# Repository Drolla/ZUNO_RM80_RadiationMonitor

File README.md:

# Z-Wave enabled Radiation, Temperature and Humidity Monitor with LCD Display

## Table of Contents

* [Description](#description)
* [Hardware required](#hardware-required)
* [Schematics, PCB layout](#schematics-pcb-layout)
* [Photos](#photos)
* [Release history](#release-history)
* [License](#license)

## Description

The project requires the following hardware components:
  * Z-Uno (Z-Wave) development board from Z-Wave.Me
  * Radiation monitor - RM-60/70/80 radiation monitor from AWARE Electronics. Connected to the external interrupt ZUNO_EXT_ZEROX.
  * Temperature/humidity sensor - DHT22 temp/hum sensor, 10kOhm resistor. Controlled via a single pin using the ZUNO_DHT module.
  * LCD display - Adafruit Sharp 1.3" Memory LCD Display. Controlled via the SPI interface.
  * Control buttons - 2 simple press buttons connected to 2 DIOs.

In addition to the functions related to the above hardware components, the application provides the following features:
  * Radiation data, temperature and humidity can be reported every minutes via Z-Wave
  * Radiation events can be indicated via the Z-Uno user LED
  * Status information can be reported via the USB attached serial interface
  * Configuration options: Z-Wave reporting, LED activity and status reporting via serial interface can individually be enabled or disabled. Configurations are stored in the EEPROM and restored after power cycling.

## Hardware required

  * Z-Uno board
  * RM-60/70/80 radiation monitor from AWARE Electronics
  * Sensor DHT11
  * LCD display - Adafruit Sharp 1.3" Memory LCD Display
  * 1 resistor1 10kOhm
  * 2 press buttons
  * Breadboard, wires

-  -  -  -  -  -  -  -  -  -  -  -  -  -  -  -  -  -  -  -  -

## Schematics, PCB layout

Schematic:

PCB layout:

Breadboard:

-  -  -  -  -  -  -  -  -  -  -  -  -  -  -  -  -  -  -  -  -

## Photos

Breadboard:

Final device:

Some display pictures:

-  -  -  -  -  -  -  -  -  -  -  -  -  -  -  -  -  -  -  -  -

## Release history

* 0.1
    * Initial version, verified with Z-Uno firmware revision 2.0.7. Since no external interrupts are supported in this firmware revision, the RM-80 radiation monitor has to be connected to the serial interface Serial0.
* 0.2
    * Version adapted for Z-Uno firmware version 2.0.9 that supports external interrupts. The RM-80 radiation monitor has to be connected to the external interrupt 'ZUNO_EXT_ZEROX'.
	 * Only valid mean/average values are reported via Z-Wave (e.g. 1-hour average value will not be reported the 1st hour after booting)

-  -  -  -  -  -  -  -  -  -  -  -  -  -  -  -  -  -  -  -  -

## License

This project is licensed under the MIT License - see the _LICENSE_ file for details.

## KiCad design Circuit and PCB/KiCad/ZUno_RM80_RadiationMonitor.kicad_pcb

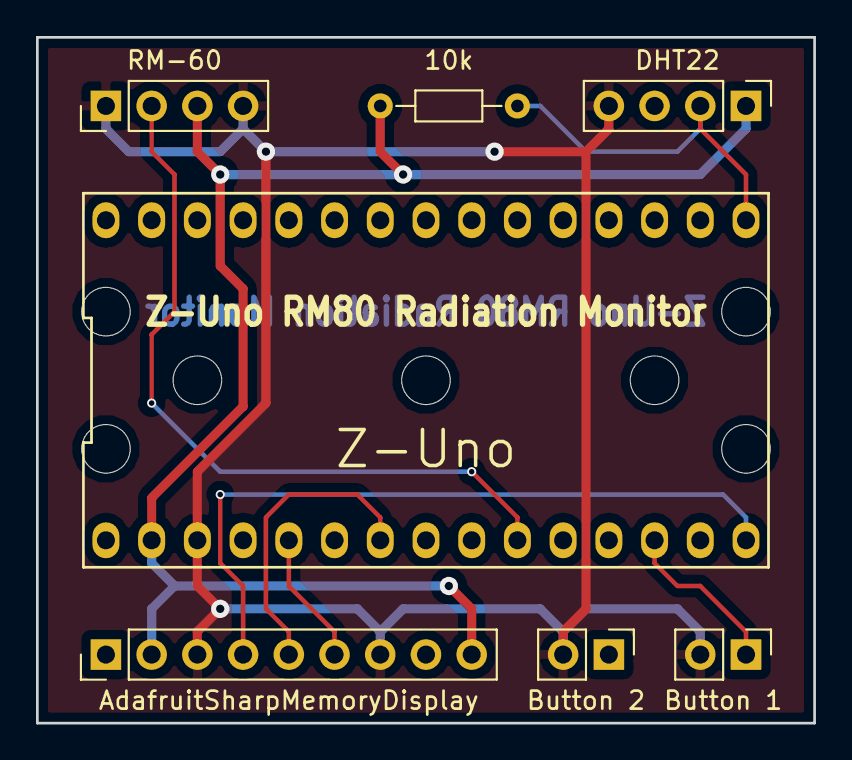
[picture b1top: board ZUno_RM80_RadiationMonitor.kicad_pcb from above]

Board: 2 copper layers, 43.2 x 38.1 mm, 7 parts (0 on the bottom side), 9 nets.

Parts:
DHT221: DHT22; Pin_Header_Straight_1x04_Pitch2.54mm
R1: 10k; R_Axial_DIN0204_L3.6mm_D1.6mm_P7.62mm_Horizontal
U1: AdafruitSharpMemoryDisplay; Pin_Header_Straight_1x09_Pitch2.54mm
U2: Z-Uno; Z-UNO
U3: RM-60; Pin_Header_Straight_1x04_Pitch2.54mm
W1: Button 2; Pin_Header_Straight_1x02_Pitch2.54mm
W2: Button 1; Pin_Header_Straight_1x02_Pitch2.54mm

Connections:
+5V: DHT221.1, R1.1, U1.2, U1.9, U2.2, U3.3
GND: DHT221.4, U1.3, U1.7, U2.3, U3.1, U3.4, W1.2, W2.2
unnamed: DHT221.2, R1.2, U2.16
unnamed: U1.4, U2.15
unnamed: U1.5, U2.7
unnamed: U1.6, U2.5
unnamed: U2.10, U3.2
unnamed: U2.12, W1.1
unnamed: U2.13, W2.1

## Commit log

2017-02-12 Documentation update
2017-02-13 Checkin the circuit and PCB data files
2017-02-13 Readme update
2017-02-13 Stack usage optimization
2017-02-13 Data logging correction: Mean values were incorrectly calculated in some situations.
2017-02-13 Completed the hardware component list in readme file
2017-02-19 Code optimizations to reduce stack usage: * setPixel * writeChrM * int2Str Performance optimization (low relevance): * writeChrS * writeChrL
2017-03-26 Version adapted for Z-Uno firmware version 2.0.9 that supports external interrupts. The RM-80 radiation monitor has to be connected to the external interrupt 'ZUNO_EXT_ZEROX'. Only valid mean/average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
2017-03-26 no message
2017-03-26 Add picture of final device
2019-09-25 Set theme jekyll-theme-cayman
